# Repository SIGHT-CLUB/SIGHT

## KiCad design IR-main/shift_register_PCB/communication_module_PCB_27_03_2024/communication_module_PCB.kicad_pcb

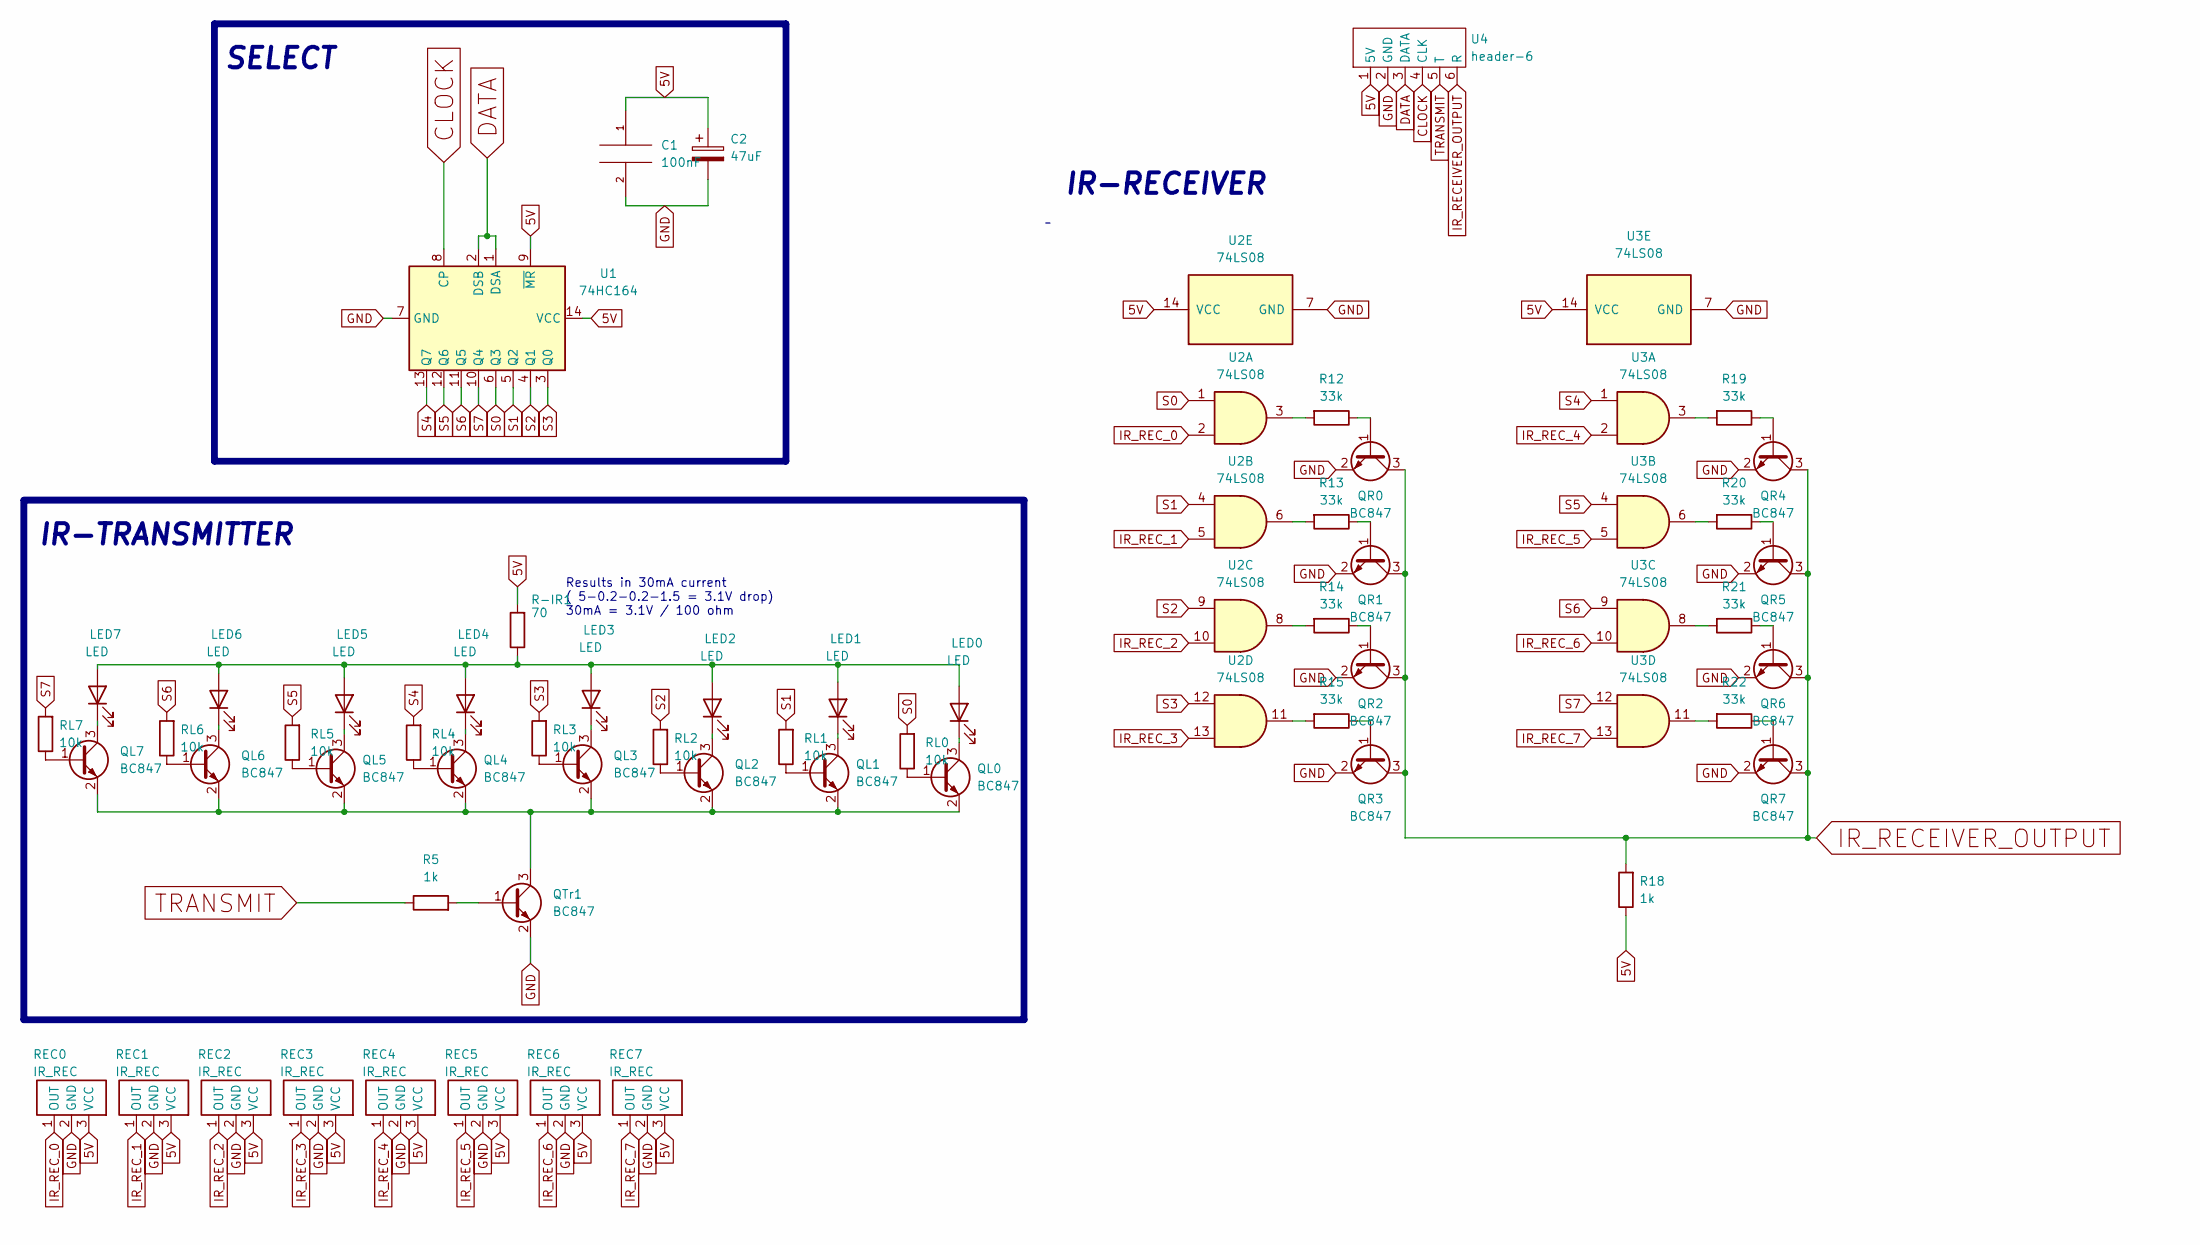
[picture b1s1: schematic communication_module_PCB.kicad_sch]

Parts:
C1: 100nF; C_Elec_6.3x5.4
C2: 47uF; C_1206_3216Metric
LED0, LED1, LED2, LED3, LED4, LED5, LED6, LED7: LED; LED_D3.0mm
QL0, QL1, QL2, QL3, QL4, QL5, QL6, QL7: BC847; SOT-23
QR0, QR1, QR2, QR3, QR4, QR5, QR6, QR7: BC847; SOT-23
QTr1: BC847; SOT-23
R5, R18: 1k; R_1206_3216Metric_Pad1.30x1.75mm_HandSolder
R12, R13, R14, R15, R19, R20, R21, R22: 33k; R_1206_3216Metric_Pad1.30x1.75mm_HandSolder
R-IR1: 70; R_1206_3216Metric_Pad1.30x1.75mm_HandSolder
REC0, REC1, REC2, REC3, REC4, REC5, REC6, REC7: IR_REC; IR-receiver
RL0, RL1, RL2, RL3, RL4, RL5, RL6, RL7: 10k; R_1206_3216Metric_Pad1.30x1.75mm_HandSolder
U1: 74HC164; DIP-14_W7.62mm
U2, U3: 74LS08; DIP-14_W7.62mm
U4: header-6; header6

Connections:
5V: C1.1, C2.1, R18.1, R-IR1.2, REC0.3 (VCC), REC1.3 (VCC), REC2.3 (VCC), REC3.3 (VCC), REC4.3 (VCC), REC5.3 (VCC), REC6.3 (VCC), REC7.3 (VCC), U1.9 (~MR), U1.14 (VCC), U2.14 (VCC), U3.14 (VCC), U4.1 (5V); also elsewhere on the board
CLOCK: U1.8 (CP), U4.4 (CLK); also elsewhere on the board
DATA: U1.1 (DSA), U1.2 (DSB), U4.3 (DATA); also elsewhere on the board
GND: C1.2, C2.2, QR0.2 (E), QR1.2 (E), QR2.2 (E), QR3.2 (E), QR4.2 (E), QR5.2 (E), QR6.2 (E), QR7.2 (E), QTr1.2 (E), REC0.2 (GND), REC1.2 (GND), REC2.2 (GND), REC3.2 (GND), REC4.2 (GND), REC5.2 (GND), REC6.2 (GND), REC7.2 (GND), U1.7 (GND), U2.7 (GND), U3.7 (GND), U4.2 (GND); also elsewhere on the board
IR_RECEIVER_OUTPUT: QR0.3 (C), QR1.3 (C), QR2.3 (C), QR3.3 (C), QR4.3 (C), QR5.3 (C), QR6.3 (C), QR7.3 (C), R18.2, U4.6 (R)
IR_REC_0: REC0.1 (OUT), U2.2
IR_REC_1: REC1.1 (OUT), U2.5
IR_REC_2: REC2.1 (OUT), U2.10
IR_REC_3: REC3.1 (OUT), U2.13
IR_REC_4: REC4.1 (OUT), U3.2
IR_REC_5: REC5.1 (OUT), U3.5
IR_REC_6: REC6.1 (OUT), U3.10
IR_REC_7: REC7.1 (OUT), U3.13
unnamed: LED0.1 (K), QL0.3 (C)
unnamed: LED1.1 (K), QL1.3 (C)
unnamed: LED2.1 (K), QL2.3 (C)
unnamed: LED3.1 (K), QL3.3 (C)
unnamed: LED4.1 (K), QL4.3 (C)
unnamed: LED5.1 (K), QL5.3 (C)
unnamed: LED6.1 (K), QL6.3 (C)
unnamed: LED7.1 (K), QL7.3 (C)
unnamed: LED0.2 (A), LED1.2 (A), LED2.2 (A), LED3.2 (A), LED4.2 (A), LED5.2 (A), LED6.2 (A), LED7.2 (A), R-IR1.1
unnamed: QL0.2 (E), QL1.2 (E), QL2.2 (E), QL3.2 (E), QL4.2 (E), QL5.2 (E), QL6.2 (E), QL7.2 (E), QTr1.3 (C)
unnamed: QTr1.1 (B), R5.2
unnamed: QR0.1 (B), R12.1
unnamed: R12.2, U2.3
unnamed: QR1.1 (B), R13.1
unnamed: R13.2, U2.6
unnamed: QR2.1 (B), R14.1
unnamed: R14.2, U2.8
unnamed: QR3.1 (B), R15.1
unnamed: R15.2, U2.11
unnamed: QR4.1 (B), R19.1
unnamed: R19.2, U3.3
unnamed: QR5.1 (B), R20.1
unnamed: R20.2, U3.6
unnamed: QR6.1 (B), R21.1
unnamed: R21.2, U3.8
unnamed: QR7.1 (B), R22.1
unnamed: R22.2, U3.11
unnamed: QL0.1 (B), RL0.1
unnamed: QL1.1 (B), RL1.1
unnamed: QL2.1 (B), RL2.1
unnamed: QL3.1 (B), RL3.1
unnamed: QL4.1 (B), RL4.1
unnamed: QL5.1 (B), RL5.1
unnamed: QL6.1 (B), RL6.1
unnamed: QL7.1 (B), RL7.1
S0: RL0.2, U1.6 (Q3), U2.1; also elsewhere on the board
S1: RL1.2, U1.5 (Q2), U2.4; also elsewhere on the board
S2: RL2.2, U1.4 (Q1), U2.9; also elsewhere on the board
S3: RL3.2, U1.3 (Q0), U2.12; also elsewhere on the board
S4: RL4.2, U1.13 (Q7), U3.1; also elsewhere on the board
S5: RL5.2, U1.12 (Q6), U3.4; also elsewhere on the board
S6: RL6.2, U1.11 (Q5), U3.9; also elsewhere on the board
S7: RL7.2, U1.10 (Q4), U3.12; also elsewhere on the board
TRANSMIT: R5.1, U4.5 (T)

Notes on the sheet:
Results in 30mA current ( 5-0.2-0.2-1.5 = 3.1V drop) 30mA = 3.1V / 100 ohm
IR-RECEIVER
SELECT
IR-TRANSMITTER

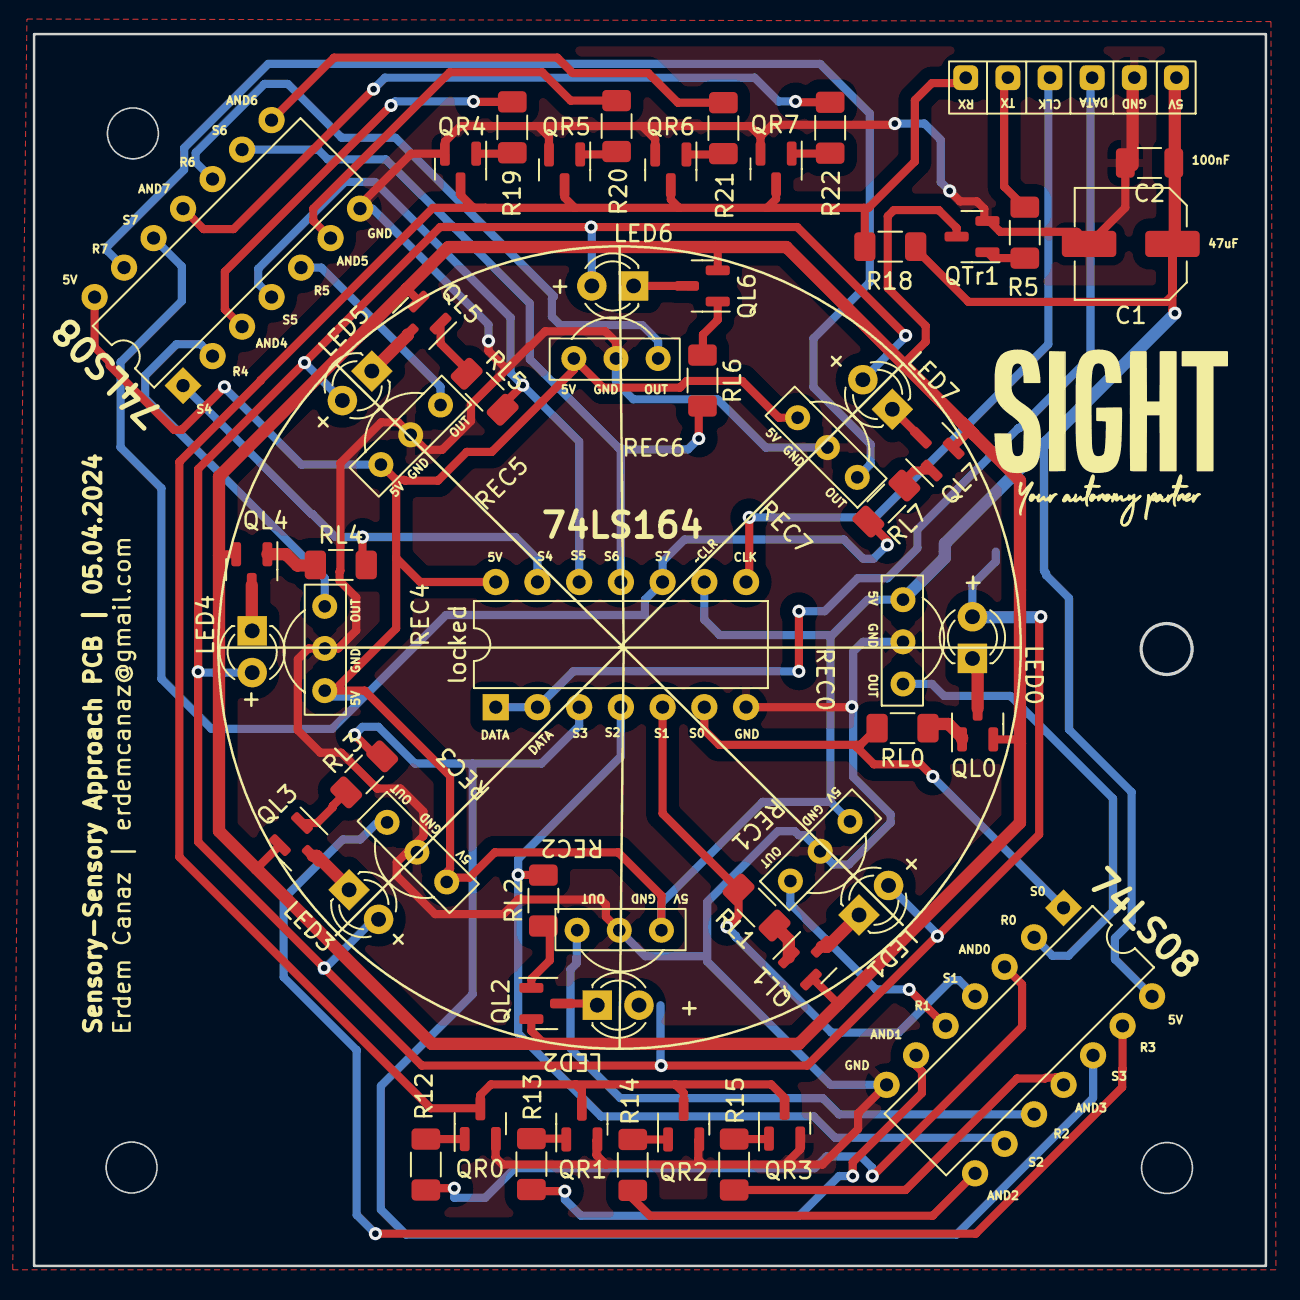
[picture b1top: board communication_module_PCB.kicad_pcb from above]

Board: 2 copper layers, 75.0 x 75.0 mm, 58 parts (1 on the bottom side), 57 nets.

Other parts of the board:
locked: 74HC164; DIP-14_W7.62mm

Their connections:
5V: locked.9 (~MR), locked.14 (VCC); also elsewhere on the board
CLOCK: locked.8 (CP); also elsewhere on the board
DATA: locked.1 (DSA), locked.2 (DSB); also elsewhere on the board
GND: locked.7 (GND); also elsewhere on the board
S0: locked.6 (Q3); also elsewhere on the board
S1: locked.5 (Q2); also elsewhere on the board
S2: locked.4 (Q1); also elsewhere on the board
S3: locked.3 (Q0); also elsewhere on the board
S4: locked.13 (Q7); also elsewhere on the board
S5: locked.12 (Q6); also elsewhere on the board
S6: locked.11 (Q5); also elsewhere on the board
S7: locked.10 (Q4); also elsewhere on the board

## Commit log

2023-12-11 Communication function
    A function to check if there is communication between to mus
2023-12-14 Compass feedback trial
2023-12-27 add comments
    added comments to case1 and moveee
2024-02-28 Add files via upload
    Ultrasonic test codes
2024-03-09 no longer wait for 5 count when listen
2024-03-09 new folder
2024-03-09 ping and listen test
2024-03-09 hopes
2024-03-11 set ping package is done
2024-03-11 Algorithm.
2024-03-11 is receiving signal is added
2024-03-11 transmitter is finished
2024-03-11 Changing the algortihm
2024-03-11 chirping test
2024-03-11 11.03.2024 - semanur
2024-03-11 Humeyra version
2024-03-18 no accumulation test
2024-03-18 Package size increased
2024-03-18 PACKET LENTGTH INCREASED TO 16
2024-03-20 alla beni
2024-03-20 Humeyra Version 20/03/24
2024-03-20 ÇALIŞAN KOD - COMMUNICATION PROTOCOL
    Çalışan bir iletişim protokolü yazıldı, 3 modül için test edildi.
2024-03-24 communication unit- PCB schematic
2024-03-27 Datasheet is added& revised PCB design is started
2024-03-27 PCB desing updated & Datasheets
2024-04-03 test
    test
2024-04-03 Some minor modifications
2024-04-04 This works for the most part
2024-04-05 PCB design
2024-04-05 Sensory-sensory approach first PCB
2024-04-06 comm unit
2024-04-10 PCB gerber
2024-04-20 Few adjustments
2024-04-20 .
    .
2024-04-20 PCB testing
2024-04-20 pcb transmit receşve testleri
2024-04-20 communication test initial
2024-04-20 birinci dönemki test ama pcb
2024-04-20 bug fix
2024-04-27 rotation with port manipulation
2024-04-29 3D designs
2024-04-30 gcodes are generated
2024-05-01 Create 1_mayis_with_rfid.ino
    Rfid ile denendi, mu hızlı gittiği için rfid kartları zamanında okuyamadı
2024-05-04 Update 1_mayis_with_rfid.ino
    BEFORE ERDEM
2024-05-04 5 mayıs
2024-05-06 DC motor speed feedback model
2024-05-06 motor speed control POF is implemented
2024-05-06 perfectly working speed control
2024-05-06 compass yeni robot
2024-05-06 erdemin while ı
2024-05-07 better speed control
2024-05-07 22:23
2024-05-07 dx - dy mesafeleri approximate ediliyor.
2024-05-08 Motors are connected
2024-05-08 move_forward_until_line_crossing
2024-05-08 move_forward_until_line_crossing is finished
2024-05-08 open loop go forward
2024-05-08 open loop turn right
2024-05-08 trial-and error code
2024-05-08 codes are working fine. But need to try with better motors
2024-05-09 Çalışan kare çizen motion unit 09_05_2024_20_02
2024-05-11 RFID Integrated version of motion unit Humo Sema Version
2024-05-11 Turning the RX fast
2024-05-11 Pıt pıt dönen
2024-05-11 12_mayis_mu_rfid
    erdemin kodu ile rfid okuma kodu birleştirildi, kod okunan her kart için sağa dönme komutu veriyor
2024-05-12 Comm Unit
    Karşılıklı iletişim mükemmel, rotatory kısmını folyo dendikten sonra tekrar bak
2024-05-12 yarımkod decision
2024-05-12 buzzer added kp changed
2024-05-12 RFID led
    led added to RFID
2024-05-12 erdem IR-demo
2024-05-12 working rotation code
2024-05-12 merging the codes
2024-05-12 shift index is printed - rotating
2024-05-12 Corrupted package is also printed
2024-05-12 02:09
2024-05-13 03:05
    .
2024-05-13 demo kodu son
2024-05-15 The motion and decision imtegrated codes. This is what we used in the demo.
2024-05-17 Humeyra version protocol
    sending 2 acks, works almost 100%, at each time we receive both the message and the ack to our sent message. This version also has a function for Erdem's IR_listen implementation.
2024-05-18 18 May version
2024-05-18 COMM FINAL VERSION FOR NOW
